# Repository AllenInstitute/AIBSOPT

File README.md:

Optical projection tomography microscope for isotropic imaging of intact, cleared mouse brains.  Designed specifically for imaging probe tracks in mouse brains following Neuropixels recordings. 

Instrument described is very low cost (~$6k US), straightforward to assemble out of mostly commercially-available parts, and with little need for maintenance or alignment.

Images acquired by this instrument can be reconstructed using free NRecon software (SkyScan via Bruker) and aligned to Allen Institute for Brain Science Common Coordinate Framework. Detecting probe tracks in these images allows registration of multiple experiments into a common spatial framework for comparing results across experiments. 

Repository contents:
- 412792_fluorSubset.gif - stack of reconstructed images from portion of mouse brain showing multiple Neuropixels tracks
- .\InstrumentBuild : 
    - Parts list
    - .\CAD : CAD design for instrument
    - .\EAGLE : Schematic for motor control shield.
    
- .\Software : 
    - .\InstrumentSoftware :  
      - .\Arduino\diyOPT : Sketch for motor driver board
      - .\MicroManager : Config file and acquisition script for data acquisition
    - .\DataProcessing : 
        - Python code to generate files + folders for NRecon reconstructions
        - Python utilities to aid in alignment using images of a test object on instrument
    - .\Analysis : Code for post-reconstruction volume registration and probe tracing 
- .\Protocols : 
  - Standard operating protocol for sample mounting, instrument operation, and reconstruction with NRecon.

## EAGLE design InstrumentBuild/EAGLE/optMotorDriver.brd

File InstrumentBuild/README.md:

Components and assembly for AIBSOPT

# CAD
	Includes STEP file of instrument assembly with all physical components and instrument rendering.  
	
	.\CAD\toMachine includes individual STEP files and drawings of parts to machine:
		- Extended motor shaft (BearingShaft.step, BearingShaftClamp.step, diyOPTShaftExplode Drawing v0.pdf). Make 1 assembly from aluminum. 
		- Motor mount (Nema17OPTmotorMountv2 v2.step and .pdf). Make 1 from aluminum. 
		- Sample holder puck (sampleHolderPuck.pdf and .step).  Make 1-4 from *magnetic* stainless steel.
		- Specimen chamber (specimenChamberBuildNotes.txt):
			DIY - slideSpecimenChamber drawing v1.pdf
			----OR----
			Purchase Hellma 50 mm large cuvette (Sigma-Aldrich part Z805750), machine OPTCuvetteBase.step, assemble CuvetteStandAssembly.step

	.\CAD\DriverBoard
		- Files to laser cut mount for optMotorButtonBoard to Imperial optical table.  Cut from acrylic and use standard PCB stand-offs to mount PCB.
		
	.\CAD\laserLaunch
		- Assemblies and build details on adding laser illumination to OPT.  Includes laser combiner + launch w/ speckle reducer and fiber coupling, enclosure, and laser illuminator.

# PCB Files

	.\EAGLE : Schematic for Arduino motor shield and remote button board for instrument control.
		- optMotorDriver BOM.txt includes parts required for assembly and links to order PCB
		- Can upload .brd files to favorite PCB fab service to order
		- Mount to optical table with .\CAD\DriverBoard part

# Notes on assembly and alignment:

Final resolution of instrument is primarily dependent on alignment of all images in the rotation stack. The rotation axis *MUST* be aligned to camera optical axis, with no roll or pitch.  Yaw is actually well-tolerated.  Roll (camera rotating around optical axis/rotational axis tilted left or right) and pitch (aka nod, rotation axis tilted towards or away from camera) manifest as misalignment in the collected image stack and blur or double-image artifacts in the reconstructions.  

Steps for aligning the roll and pitch axes follow those well-described in https://doi.org/10.1371/journal.pone.0073491.  An object, such as a small ball bearing or tip of a hypodermic needle mounted on the sample holder using glue and/or magnets, provides a good fiducial marker.  This item or a feature on it should be able to be localized in images to sub-pixel precision.  Tracking this feature through the stack should produce a straight line parallel to one axis of the camera.  Any tilt is evidence of roll; elliptical character evidence of pitch.  The .\Software\DataProcessing\assessTestObject.py script is helpful in this step.

Adjustments can be made through small movements of the XY stage and motor.  This assembly should rest equally on all four of the shaft collars on the 1/2" mounting posts.  Typically the screws in the post holders are left open so that the posts freely drop to the proper position.  Shims made from shim stock or a cleaned and dissected soda can make small adjustments to the stage tip or tilt for testing alignment.  If a good position is found, this can be set in place by tightening the post holder screws with the shims in place, removing the shims, then lowering the shaft collars hard against the post holders before tightening the collar screws.  Then when the stage is lifted out and returned, it should return to the same position defined by the shaft collars against the top of the post holders.

Additional care must be taken to have specimen remain within camera field of view while rotating and remain in focus.  Both are straightforward to deal with using the adjusters on the XY stage.  The depth of focus can be increased using the built-in aperture iris on the telecentric lens.  Best to have this be close to the full depth of the specimen without overly darkening the images.  In practice the lost sharpness in the images is negligable compared to the blur induced by mis-alignment.

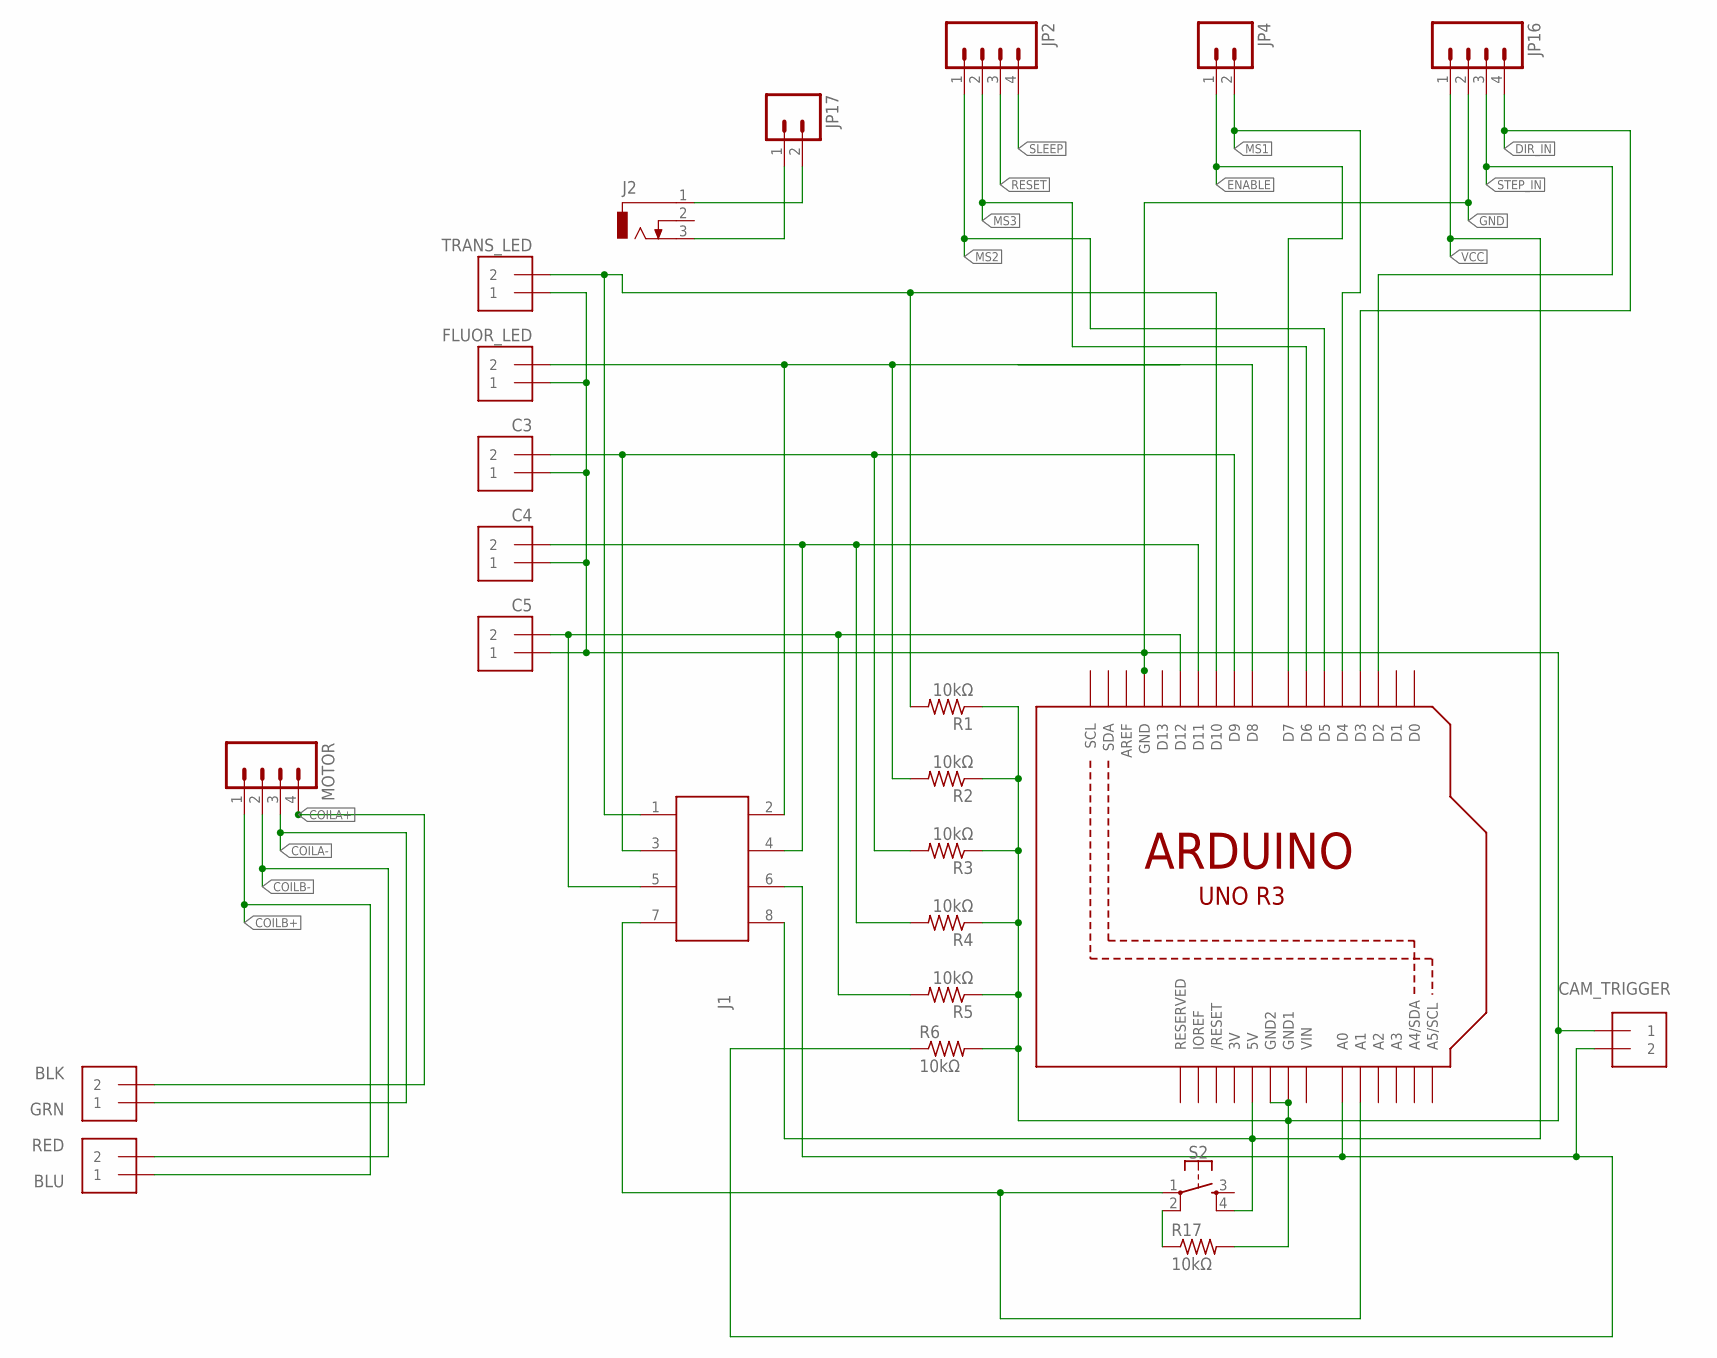
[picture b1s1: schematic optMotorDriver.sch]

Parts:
ACOIL: 1X2-3.5MM
BCOIL: 1X2-3.5MM
C1, C2, C3, C4, C5: 1X2-3.5MM
J1: 62400821722
J2: DCJ0303
JP2, JP16: M04PTH; 1X04
JP4, JP17: M02PTH; 1X02
MOTOR: M04PTH; 1X04
R1, R2, R3, R4, R5, R6, R17: 10kΩ; R1206
S2: MOMENTARY-SWITCH-SPST-2-SMD-5.2MM; TACTILE_SWITCH_SMD_5.2MM
TRIGGER: 1X2-3.5MM
U1: ARDUINOR3-DIMENSION; ARDUINOR3

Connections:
3V: U1.3V
COILA+: ACOIL.2, MOTOR.4
COILA-: ACOIL.1, MOTOR.3
COILB+: BCOIL.1, MOTOR.1
COILB-: BCOIL.2, MOTOR.2
DIR_IN: JP16.4, U1.D3
ENABLE: JP4.1, U1.D7
GND: C1.1, C2.1, C3.1, C4.1, C5.1, JP16.2, R1.1, R2.1, R3.1, R4.1, R5.1, R6.2, R17.2, TRIGGER.1, U1.GND, U1.GND1, U1.GND2
MS1: JP4.2, U1.D4
MS2: JP2.1, U1.D5
MS3: JP2.2, U1.D6
unnamed: J2.3, JP17.1
unnamed: C4.2, J1.4 (6), R4.2, U1.D11
unnamed: J2.1, JP17.2
unnamed: C3.2, J1.3 (5), R3.2, U1.D9
unnamed: C5.2, J1.5 (3), R5.2, U1.D12
unnamed: J1.7 (1), S2.1, U1.A1
unnamed: J1.6 (4), R6.1, TRIGGER.2, U1.A0
unnamed: C2.2, J1.2 (8), R2.2, U1.D8
unnamed: C1.2, J1.1 (7), R1.2, U1.D10
unnamed: R17.1, S2.2
RESET: JP2.3
SLEEP: JP2.4
STEP_IN: JP16.3, U1.D2
VCC: J1.8 (2), JP16.1, S2.4, U1.5V
VIN: U1.VIN

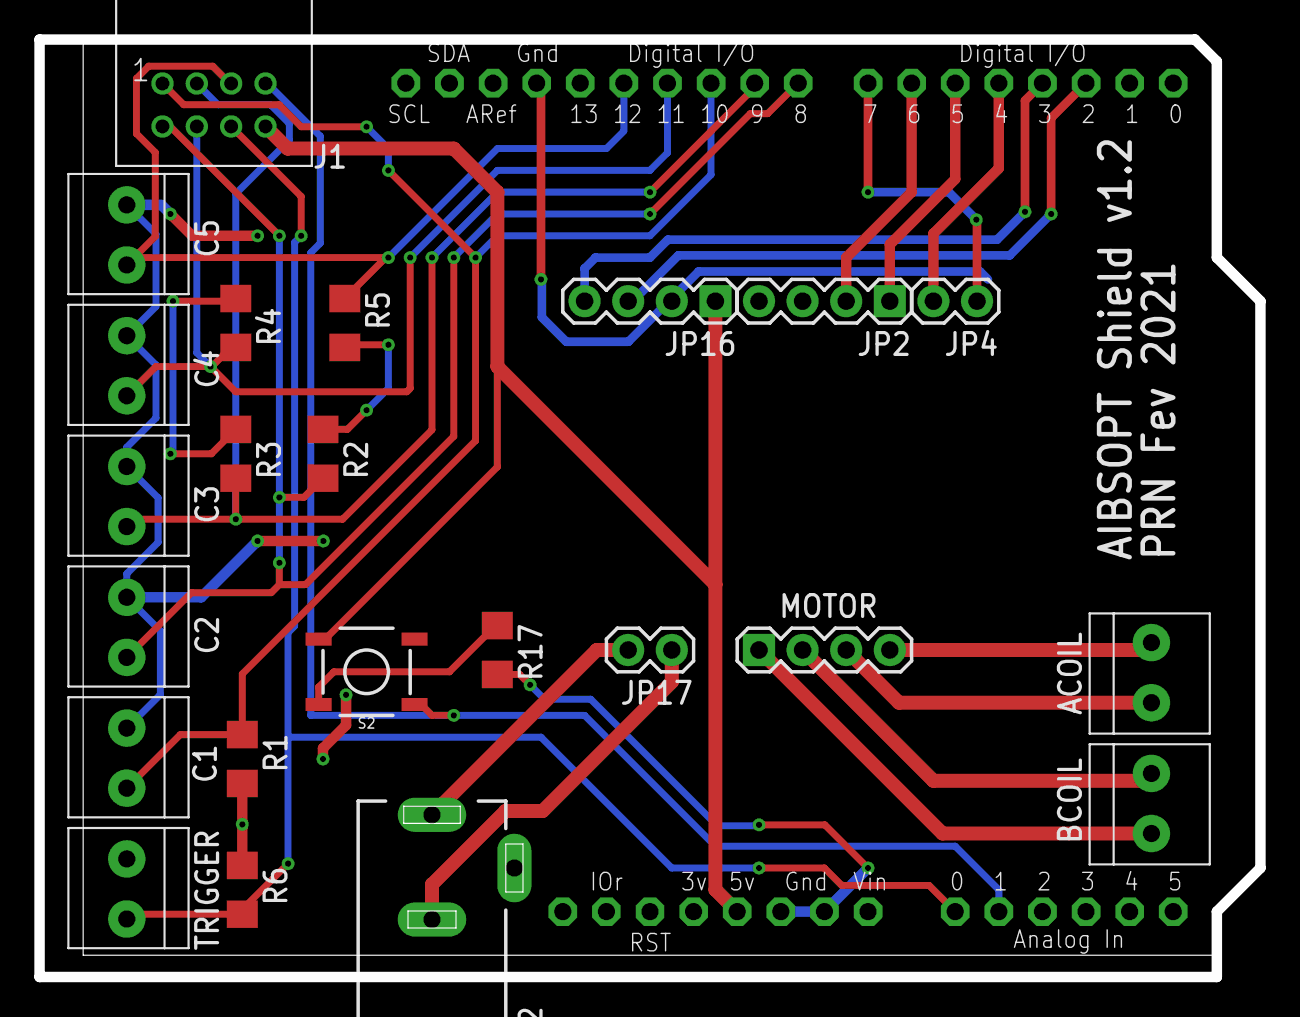
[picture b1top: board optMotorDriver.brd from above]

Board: 2 copper layers, 71.1 x 54.6 mm, 24 parts (0 on the bottom side), 22 nets.

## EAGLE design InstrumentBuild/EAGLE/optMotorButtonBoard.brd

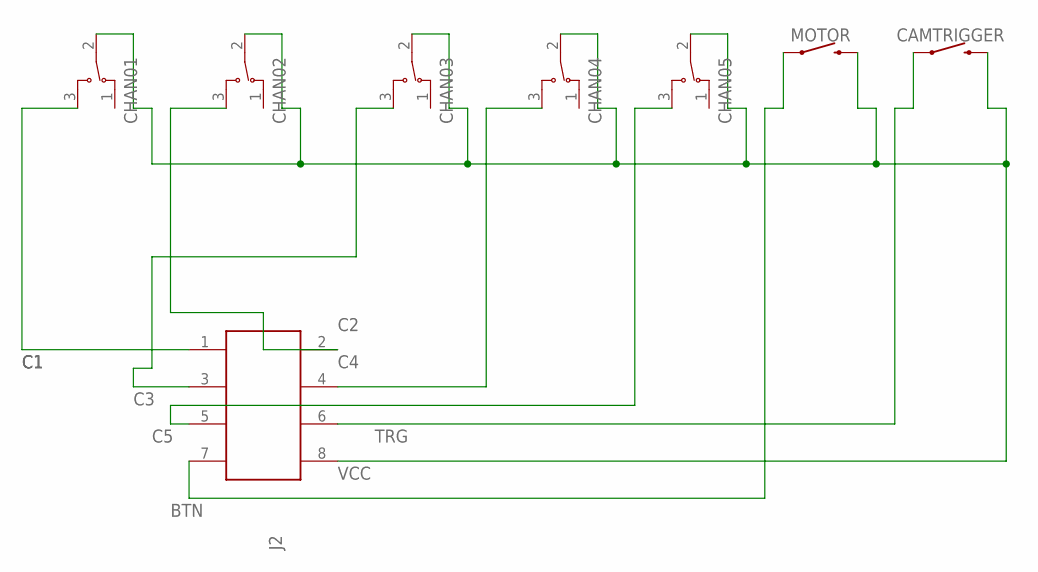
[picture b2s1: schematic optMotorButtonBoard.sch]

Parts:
CAMTRIGGER: MOMENTARY-SWITCH-SPST-PTH-12MM; TACTILE_SWITCH_PTH_12MM
CHAN01, CHAN02, CHAN03, CHAN04, CHAN05: ATE1E-2M3-10-Z
J2: 62400821722
MOTOR: MOMENTARY-SWITCH-SPST-PTH-12MM; TACTILE_SWITCH_PTH_12MM

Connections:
BTN: J2.7 (1), MOTOR.1
C1: CHAN01.3, J2.1 (7)
C2: CHAN02.3, J2.2 (8)
C3: CHAN03.3, J2.3 (5)
C4: CHAN04.3, J2.4 (6)
C5: CHAN05.3, J2.5 (3)
TRG: CAMTRIGGER.1, J2.6 (4)
VCC: CAMTRIGGER.3 (2), CHAN01.2, CHAN02.2, CHAN03.2, CHAN04.2, CHAN05.2, J2.8 (2), MOTOR.3 (2)

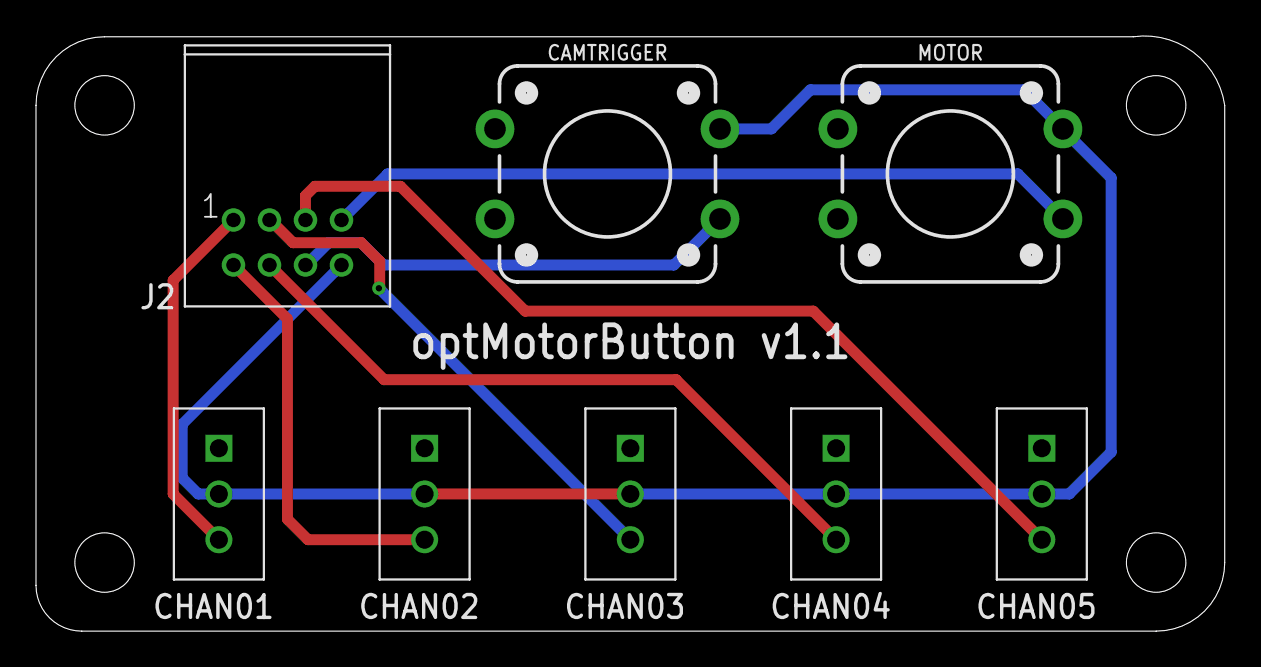
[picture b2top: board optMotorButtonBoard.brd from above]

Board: 2 copper layers, 66.0 x 33.1 mm, 12 parts (0 on the bottom side), 8 nets.

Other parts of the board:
U$1, U$2, U$3, U$4: STAND-OFF

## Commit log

2019-09-28 Initial commit to repo.
2019-10-14 Create README.md
    Added readme for CAD and assembly parts.
2019-10-15 Reorg and clean-up prior to release. Removed excess CAD files from commercial makers. Added software for alignment and post-processing of images as acquired by MicroManager files. Renamed folders to 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
2019-10-15 Update README.md
    Expanding main Readme prior to release.
2019-10-15 Added example gif. Removed incorrect schematic file.
2019-10-15 Filling in instrument build readme.
2019-10-15 Add analysis code
2019-10-16 Final modification of software readme.md prior to setting repo to public.
2020-01-30 Updated diyOPT.ino file to reflect changes for motor driver PCB.
2020-01-30 Update schematics and readme for driver board.
2020-01-30 Add files for driver board, button board, and BOM.
2020-01-30 Added files for mount for optButtonBoard
2020-01-30 Update readme files to include motor driver PCB information
2020-01-30 Update header of Arduino sketch.
2020-01-30 Added license files.
2020-03-10 Replace license, contribution agreement files with .docx files. Add laserLaunch folders and files. Add CAD files and update specimenChamberBuildNotes.txt to support commercial cuvette.
2020-03-10 Added sheet for laserLaunch in ./InstrumentBuild/PartsList20181210.xlsx. Sheet contains no data.
2020-05-14 Update optMotorDriver BOM.txt
    Correct links to PCBs
2020-08-14 Add pre-processing app
2020-08-20 Replace requirements.txt with environment.yml
2020-09-01 Remove dependencies not available on Windows
2020-09-04 Add multiple views to annotation app
2020-09-04 Fix bug in TIFF file search string
2020-09-11 Remove unused 'pwd' import
2021-01-07 Change color for probe B1
2021-01-07 Change color for B probes
2021-01-22 Remove unused code
2021-01-22 Split out code into functions
2021-01-22 Add vtk requirement
2021-01-22 Code cleanup
2021-01-28 Add axis labels
2021-02-20 Updated top silk and added board's name to top.
2021-02-20 Updated top silk, removed some layout corners and increased version to 1.2.
2022-01-13 Update preprocessing app for new OPT system
2022-01-13 Add back fluor
2022-01-24 Add option to mirror image when loading
2022-01-27 Change location of image flip

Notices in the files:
parts and their libraries:
SparkFun-Switches: Licensing: Creative Commons ShareAlike 4.0 International - https://creativecommons.org/licenses/by-sa/4.0
Wurth_Elektronik_Electromechanic_Wire_to: Copyright: Würth Elektronik
